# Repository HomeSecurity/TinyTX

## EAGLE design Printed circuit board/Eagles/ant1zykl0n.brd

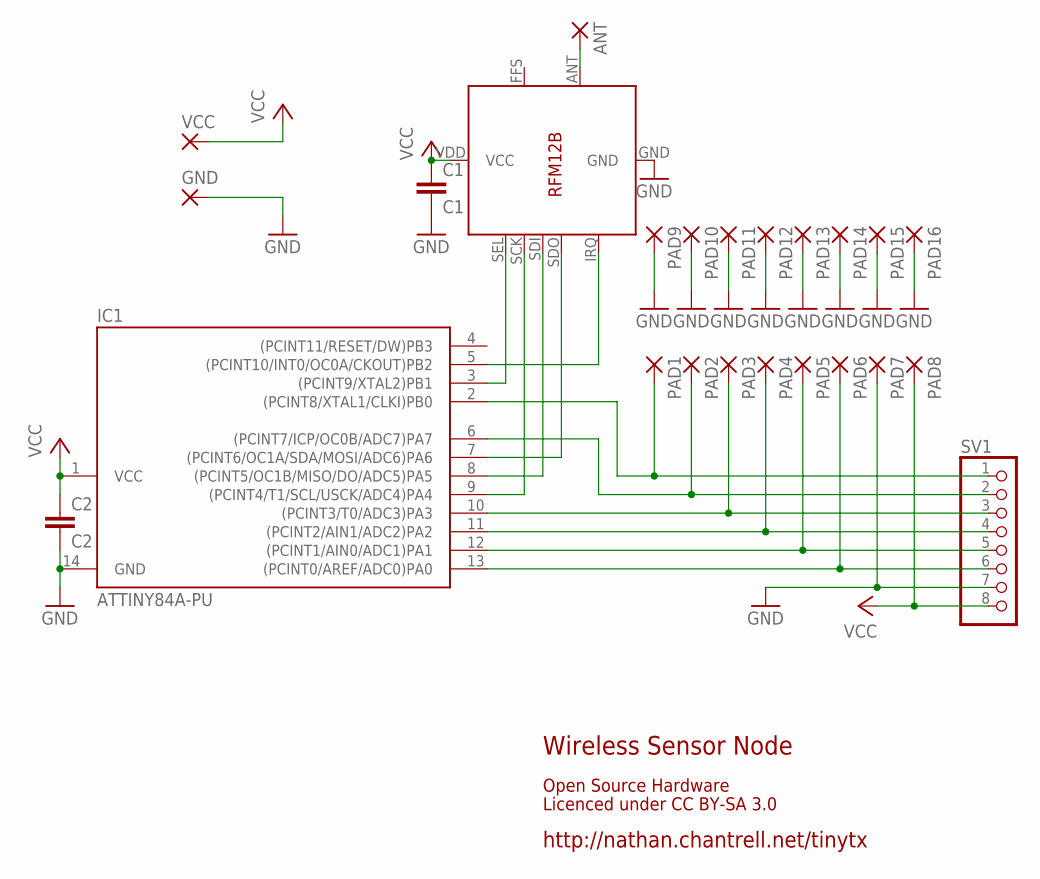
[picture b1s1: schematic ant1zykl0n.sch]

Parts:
ANT: 2,15/1,0
C1: C1; C025-025X050
C2: C2; C025-025X050
GND: 2,15/1,0
IC1: ATTINY84A-PU; DIL14
PAD1, PAD2, PAD3, PAD4, PAD5, PAD6, PAD7, PAD8, PAD9, PAD10, PAD11, PAD12, PAD13, PAD14, PAD15, PAD16: 1,6/0,9
SV1: PINHD-1X8; 1X08
U$1: RFM12B
VCC: 2,15/1,0

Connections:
GND: C1.2, C2.2, GND.1, IC1.14 (GND), PAD7.1, PAD9.1, PAD10.1, PAD11.1, PAD12.1, PAD13.1, PAD14.1, PAD15.1, PAD16.1, SV1.7, U$1.GND
unnamed: IC1.3 ((PCINT9/XTAL2)PB1), U$1.SEL
unnamed: IC1.5 ((PCINT10/INT0/OC0A/CKOUT)PB2), U$1.IRQ
unnamed: IC1.8 ((PCINT5/OC1B/MISO/DO/ADC5)PA5), U$1.SDI
unnamed: IC1.7 ((PCINT6/OC1A/SDA/MOSI/ADC6)PA6), U$1.SDO
unnamed: ANT.1, U$1.ANT
unnamed: IC1.9 ((PCINT4/T1/SCL/USCK/ADC4)PA4), U$1.SCK
unnamed: IC1.6 ((PCINT7/ICP/OC0B/ADC7)PA7), PAD2.1, SV1.2
unnamed: IC1.13 ((PCINT0/AREF/ADC0)PA0), PAD6.1, SV1.6
unnamed: IC1.12 ((PCINT1/AIN0/ADC1)PA1), PAD5.1, SV1.5
unnamed: IC1.2 ((PCINT8/XTAL1/CLKI)PB0), PAD1.1, SV1.1
unnamed: IC1.11 ((PCINT2/AIN1/ADC2)PA2), PAD4.1, SV1.4
unnamed: IC1.10 ((PCINT3/T0/ADC3)PA3), PAD3.1, SV1.3
VCC: C1.1, C2.1, IC1.1 (VCC), PAD8.1, SV1.8, U$1.VDD (VCC), VCC.1

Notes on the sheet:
http://nathan.chantrell.net/tinytx
Wireless Sensor Node
Licenced under CC BY-SA 3.0
Open Source Hardware

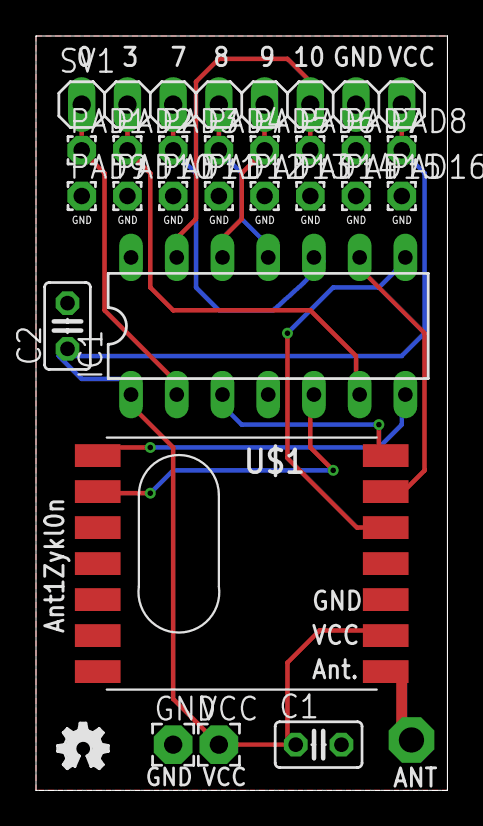
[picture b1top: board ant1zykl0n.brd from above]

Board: 2 copper layers, 22.9 x 41.9 mm, 25 parts (0 on the bottom side), 14 nets.

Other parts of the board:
U$2: OSHW_FILLX100_NOTEXT

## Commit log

2017-05-08 initial
2017-06-10 Raspberry -> master radio node UART communication
2017-06-11 100% fixed receiver (aktor) & master code (master -> aktor)
2017-06-19 fixed receive
2017-06-24 added led for reed
